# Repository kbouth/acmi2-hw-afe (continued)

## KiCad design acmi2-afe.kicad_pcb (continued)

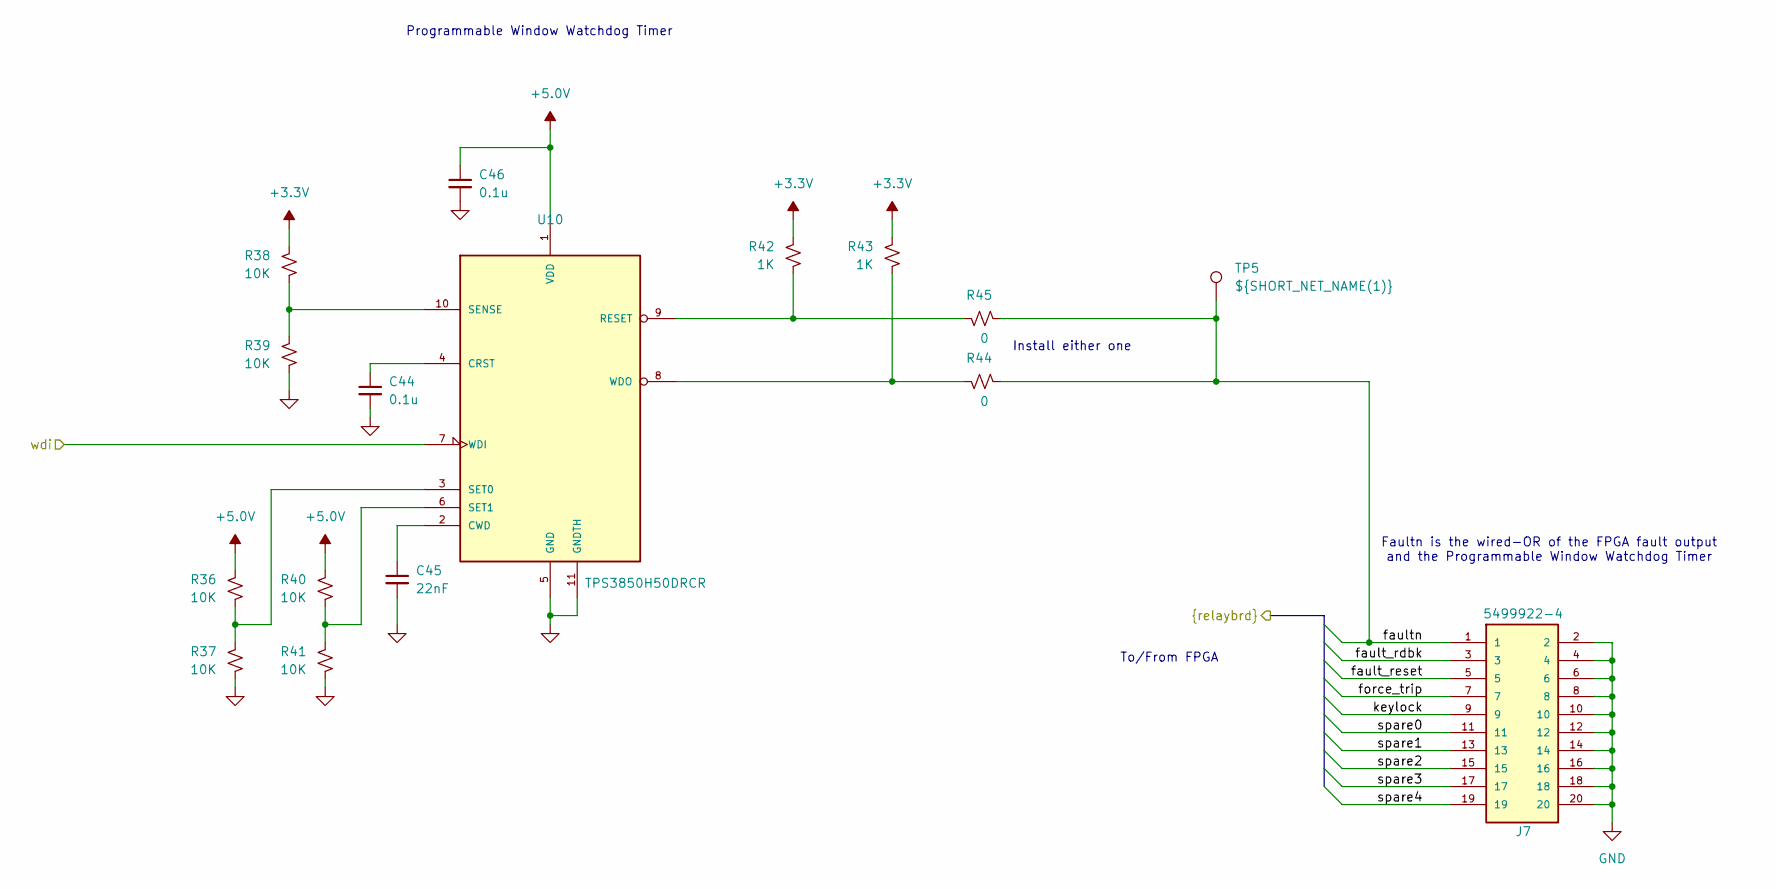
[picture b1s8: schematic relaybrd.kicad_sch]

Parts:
C44, C46: 0.1u; C_0805_2012Metric; MFG_PN TMF212B7104KGHT
C45: 22nF; C_0805_2012Metric; MFG_PN C0805C223J3GEC7210
J7: 5499922-4; TE_5499922-4; PARTREV R
R36, R37, R38, R39, R40, R41: 10K; R_0805_2012Metric; MFG_PN ERJ-2RKF1001X
R42, R43: 1K; R_0805_2012Metric; MFG_PN ERJ-P06F1001V
R44, R45: 0; R_0805_2012Metric; MFG_PN ERJ-2GE0R00X
TP5: ${SHORT_NET_NAME(1)}; TestPoint_RCS-0C; MFG_PN RCS-0C
U10: TPS3850H50DRCR; TPS3850_DRCR; MFG_PN TPS3850H33DRCR

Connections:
+3.3V: R38.1, R42.1, R43.1; also elsewhere on the board
+5.0V: C46.1, R36.1, R40.1, U10.1 (VDD); also elsewhere on the board
/Relay Board Interface/fault_rdbk: J7.3; also elsewhere on the board
/Relay Board Interface/fault_reset: J7.5; also elsewhere on the board
/Relay Board Interface/faultn: J7.1, R44.2, R45.2, TP5.1 (1_1); also elsewhere on the board
/Relay Board Interface/force_trip: J7.7; also elsewhere on the board
/Relay Board Interface/keylock: J7.9; also elsewhere on the board
/Relay Board Interface/spare0: J7.11; also elsewhere on the board
/Relay Board Interface/spare1: J7.13; also elsewhere on the board
/Relay Board Interface/spare2: J7.15; also elsewhere on the board
/Relay Board Interface/spare3: J7.17; also elsewhere on the board
/Relay Board Interface/spare4: J7.19; also elsewhere on the board
/Relay Board Interface/wdi: U10.7 (WDI); also elsewhere on the board
GND: C44.2, C45.2, C46.2, J7.2, J7.4, J7.6, J7.8, J7.10, J7.12, J7.14, J7.16, J7.18, J7.20, R37.2, R39.2, R41.2, U10.5 (GND), U10.11 (GNDTH); also elsewhere on the board
unnamed: C44.1, U10.4 (CRST)
unnamed: C45.1, U10.2 (CWD)
unnamed: R42.2, R45.1, U10.9 (RESET)
unnamed: R38.2, R39.1, U10.10 (SENSE)
unnamed: R36.2, R37.1, U10.3 (SET0)
unnamed: R40.2, R41.1, U10.6 (SET1)
unnamed: R43.2, R44.1, U10.8 (WDO)

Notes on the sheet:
To/From FPGA
Faultn is the wired-OR of the FPGA fault output and the Programmable Window Watchdog Timer
Install either one
Programmable Window Watchdog Timer

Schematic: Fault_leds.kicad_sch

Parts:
C34, C35, C36, C37: 0.1u; C_0805_2012Metric; MFG_PN TMF212B7104KGHT
D2, D3, D4, D5, D6, D7, D8, D9, D10, D11, D12, D13, D14, D15, D16, D17: RED; LED_0805_2012Metric; MFG_PN LTST-C191KGKT
R11, R12, R13, R14, R15, R16, R17, R18, R19, R20, R21, R22, R23, R24, R25, R26: 680; R_0805_2012Metric; MFG_PN ERJ-6ENF6800V
U7: SN74LVC16T245DGGR; SOP50P810X120-48N; MFG_PN SN74LVC16T245DGGR

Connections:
+1.8V: C34.1, C35.1, U7.7 (VCCB_7), U7.18 (VCCB_18); also elsewhere on the board
+3.3V: C36.1, C37.1, U7.31 (VCCA_31), U7.42 (VCCA_42); also elsewhere on the board
/Fault LED's/fault_led0: U7.2 (1B1); also elsewhere on the board
/Fault LED's/fault_led1: U7.3 (1B2); also elsewhere on the board
/Fault LED's/fault_led2: U7.5 (1B3); also elsewhere on the board
/Fault LED's/fault_led3: U7.6 (1B4); also elsewhere on the board
/Fault LED's/fault_led4: U7.8 (1B5); also elsewhere on the board
/Fault LED's/fault_led5: U7.9 (1B6); also elsewhere on the board
/Fault LED's/fault_led6: U7.11 (1B7); also elsewhere on the board
/Fault LED's/fault_led7: U7.12 (1B8); also elsewhere on the board
/Fault LED's/fault_led8: U7.13 (2B1); also elsewhere on the board
/Fault LED's/fault_led9: U7.14 (2B2); also elsewhere on the board
/Fault LED's/fault_led10: U7.16 (2B3); also elsewhere on the board
/Fault LED's/fault_led11: U7.17 (2B4); also elsewhere on the board
/Fault LED's/fault_led12: U7.19 (2B5); also elsewhere on the board
/Fault LED's/fault_led13: U7.20 (2B6); also elsewhere on the board
/Fault LED's/fault_led14: U7.22 (2B7); also elsewhere on the board
/Fault LED's/fault_led15: U7.23 (2B8); also elsewhere on the board
GND: C34.2, C35.2, C36.2, C37.2, D2.1 (K), D3.1 (K), D4.1 (K), D5.1 (K), D6.1 (K), D7.1 (K), D8.1 (K), D9.1 (K), D10.1 (K), D11.1 (K), D12.1 (K), D13.1 (K), D14.1 (K), D15.1 (K), D16.1 (K), D17.1 (K), U7.1 (1DIR), U7.4 (GND), U7.10 (GND), U7.15 (GND), U7.21 (GND), U7.24 (2DIR), U7.25 (2~OE), U7.28 (GND), U7.34 (GND), U7.39 (GND), U7.45 (GND), U7.48 (1~OE); also elsewhere on the board
unnamed: D2.2 (A), R11.2
unnamed: D3.2 (A), R12.2
unnamed: D4.2 (A), R13.2
unnamed: D5.2 (A), R14.2
unnamed: D6.2 (A), R15.2
unnamed: D7.2 (A), R16.2
unnamed: D8.2 (A), R17.2
unnamed: D9.2 (A), R18.2
unnamed: D10.2 (A), R19.2
unnamed: D11.2 (A), R20.2
unnamed: D12.2 (A), R21.2
unnamed: D13.2 (A), R22.2
unnamed: D14.2 (A), R23.2
unnamed: D15.2 (A), R24.2
unnamed: D16.2 (A), R25.2
unnamed: D17.2 (A), R26.2
unnamed: R11.1, U7.47 (1A1)
unnamed: R12.1, U7.46 (1A2)
unnamed: R13.1, U7.44 (1A3)
unnamed: R14.1, U7.43 (1A4)
unnamed: R15.1, U7.41 (1A5)
unnamed: R16.1, U7.40 (1A6)
unnamed: R17.1, U7.38 (1A7)
unnamed: R18.1, U7.37 (1A8)
unnamed: R19.1, U7.36 (2A1)
unnamed: R20.1, U7.35 (2A2)
unnamed: R21.1, U7.33 (2A3)
unnamed: R22.1, U7.32 (2A4)
unnamed: R23.1, U7.30 (2A5)
unnamed: R24.1, U7.29 (2A6)
unnamed: R25.1, U7.27 (2A7)
unnamed: R26.1, U7.26 (2A8)

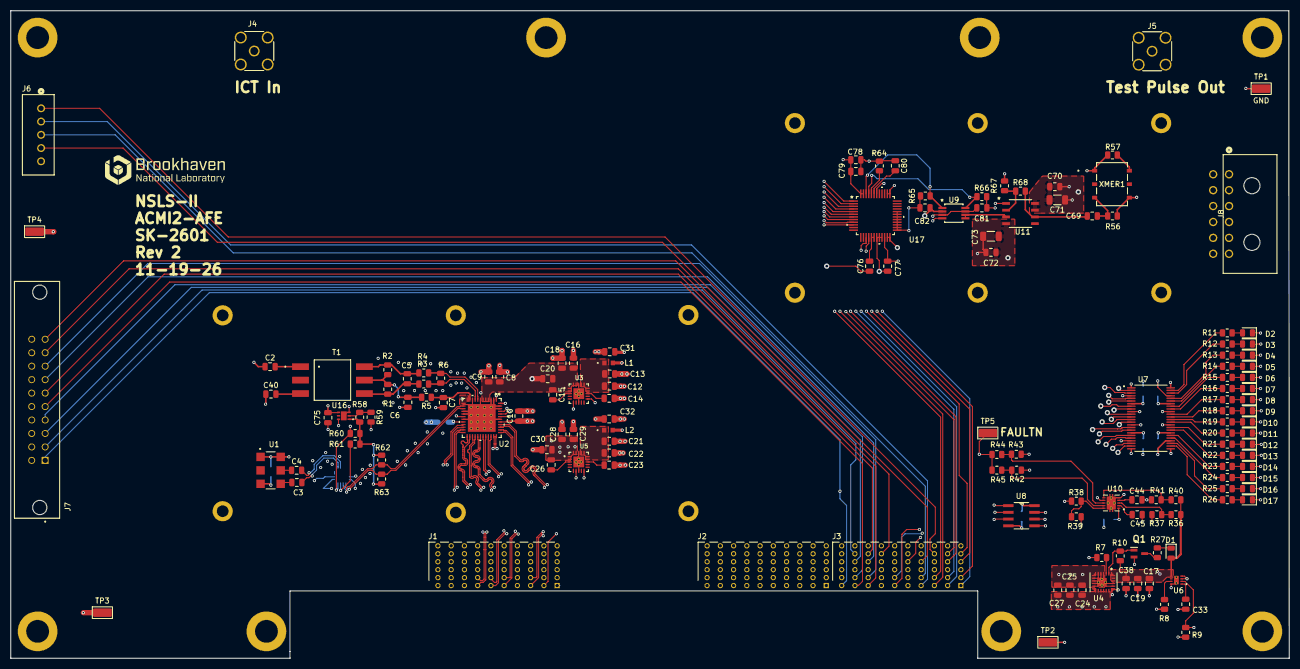
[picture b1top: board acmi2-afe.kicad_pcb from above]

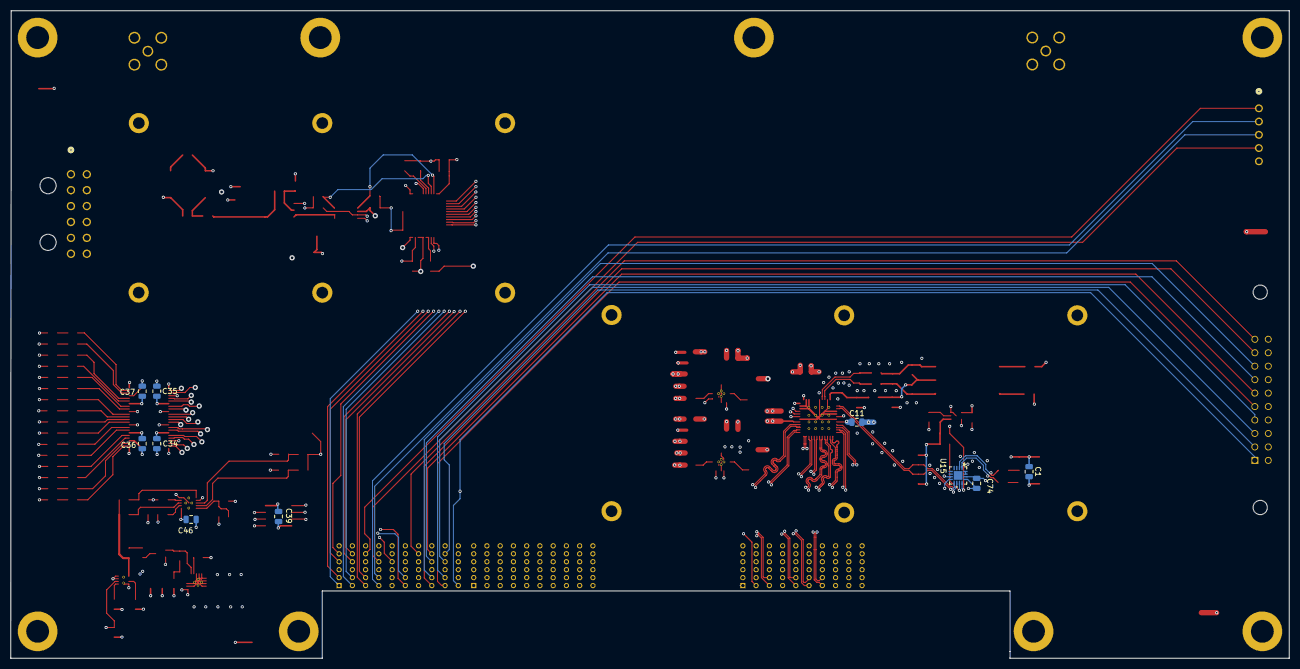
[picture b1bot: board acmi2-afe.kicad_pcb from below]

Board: 6 copper layers, 241.3 x 122.2 mm, 176 parts (10 on the bottom side), 163 nets.
